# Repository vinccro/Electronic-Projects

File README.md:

# Electronic-Projects
Schematics and PCB board designs

The esp32SimpleRelay is a project that works from a 12v source probably a 
battery/solar setup. This is wifi so must be close to a wifi router or similar. 
Basicly a simple on/off relay, maybe for 12v led lights .
--currently esp32
--could use
  --zigbee (too expensive, long range, mesh network)
  --NRF24L01 (cheap, short range, star network)
  --433MHz modules (super cheap, long range, not a transceiver)
  --lora module ( expensive, long range, mesh network)
 
The tabelmini is a motor, valve etc. controller. Not designed yet to be for
industrial work. How it works: uses buttons to selected preprogrammed motor etc.
and user can select tests to be performed. or control the motor etc. directly. 
Possible connects to a PLC that controls the motor etc. and sends it commands 
wirelessly. or Directly connect using a port.
(working progress)

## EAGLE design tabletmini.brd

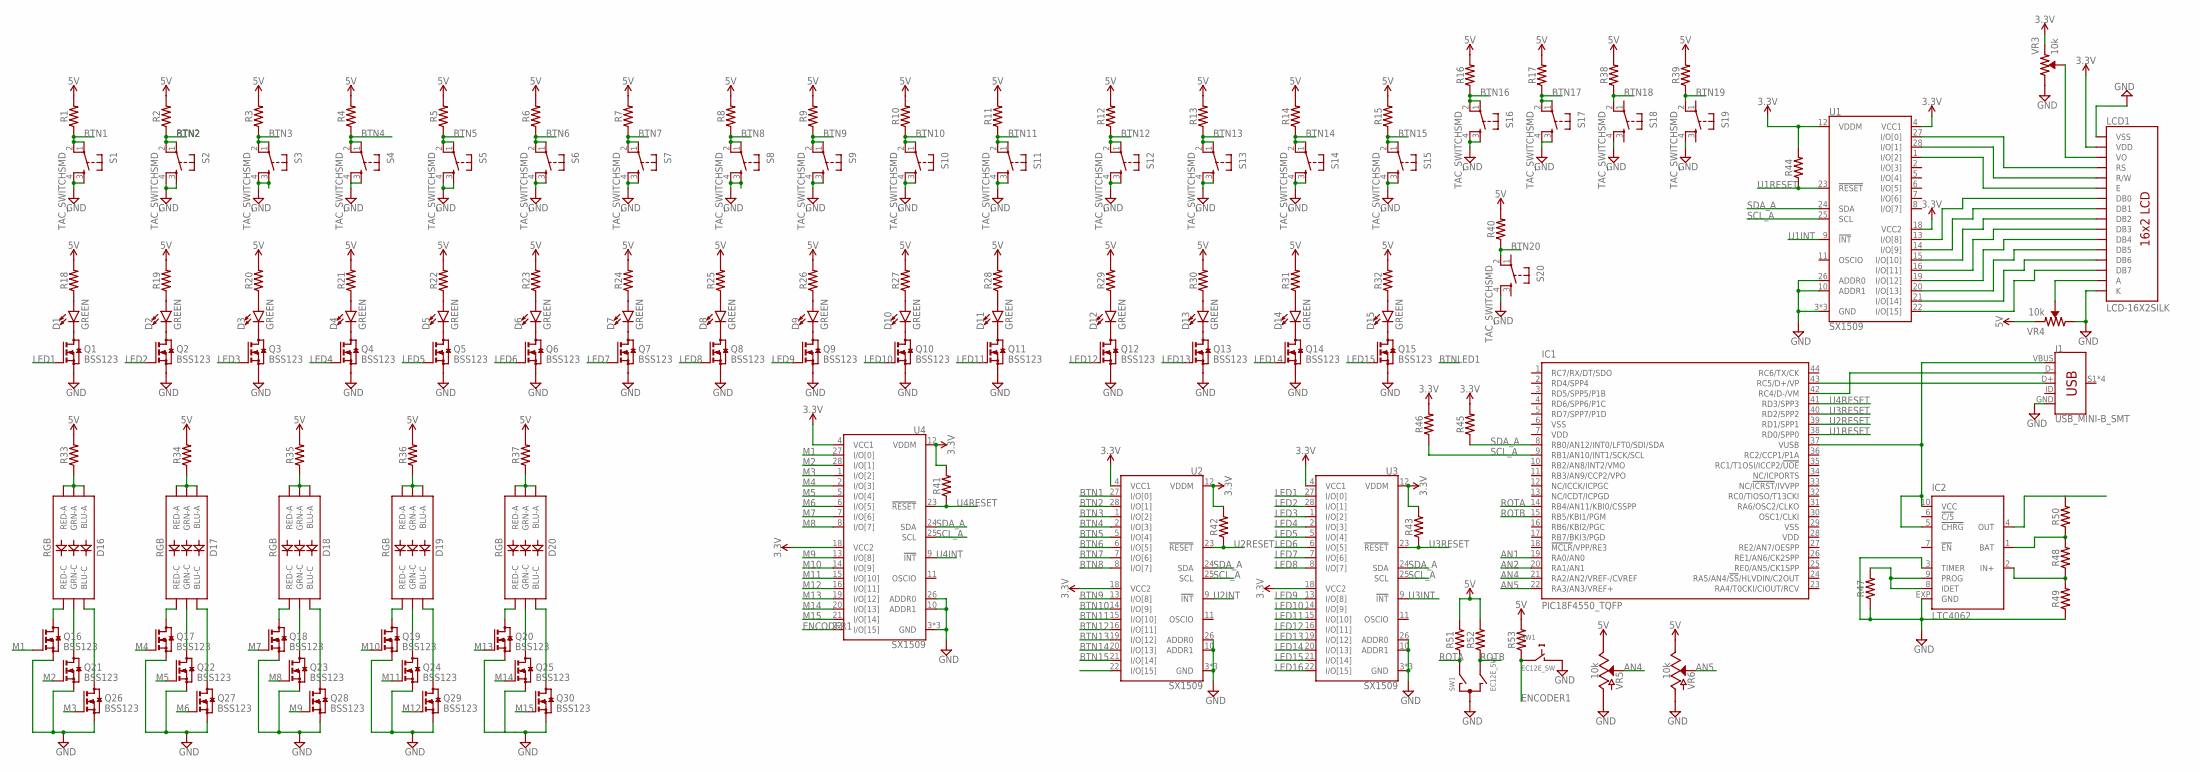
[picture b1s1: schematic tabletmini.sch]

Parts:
D1, D2, D3, D4, D5, D6, D7, D8, D9, D10, D11, D12, D13, D14, D15: GREEN; LED-1206
D16, D17, D18, D19, D20: RGB; PLCC-6-LED
IC1: PIC18F4550_TQFP; TQFP44
IC2: LTC4062; DFN10-3X3
J1: USB_MINI-B_SMT; USB-MINIB
LCD1: LCD-16X2SILK; LCD-16X2
Q1, Q2, Q3, Q4, Q5, Q6, Q7, Q8, Q9, Q10, Q11, Q12, Q13, Q14, Q15, Q16, Q17, Q18, Q19, Q20, Q21, Q22, Q23, Q24, Q25, Q26, Q27, Q28, Q29, Q30: BSS123; SOT23
R1, R2, R3, R4, R5, R6, R7, R8, R9, R10, R11, R12, R13, R14, R15, R16, R17, R18, R19, R20, R21, R22, R23, R24, R25, R26, R27, R28, R29, R30, R31, R32, R33, R34, R35, R36, R37, R38, R39, R40, R41, R42, R43, R44, R45, R46, R47, R48, R49, R50, R51, R52, R53: 1206
S1, S2, S3, S4, S5, S6, S7, S8, S9, S10, S11, S12, S13, S14, S15, S16, S17, S18, S19, S20: TAC_SWITCHSMD; TACTILE-SWITCH-SMD
SW1: EC12E_SW; ALPS_EC12E_SW
U1, U2, U3, U4: SX1509; QFN-28
VR3, VR4: 10k; TRIMPOT-SMD-3MM-CLOSED
VR5, VR6: 10k; POT-PTH-ALPS-KIT

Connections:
3.3V: LCD1.2 (VDD), R41.2, R42.2, R43.2, R44.2, R45.2, R46.2, U1.4 (VCC1), U1.12 (VDDM), U1.18 (VCC2), U2.4 (VCC1), U2.12 (VDDM), U2.18 (VCC2), U3.4 (VCC1), U3.12 (VDDM), U3.18 (VCC2), U4.4 (VCC1), U4.12 (VDDM), U4.18 (VCC2), VR3.1 (CCW)
5V: R1.2, R2.2, R3.2, R4.2, R5.2, R6.2, R7.2, R8.2, R9.2, R10.2, R11.2, R12.2, R13.2, R14.2, R15.2, R16.2, R17.2, R18.2, R19.2, R20.2, R21.2, R22.2, R23.2, R24.2, R25.2, R26.2, R27.2, R28.2, R29.2, R30.2, R31.2, R32.2, R33.2, R34.2, R35.2, R36.2, R37.2, R38.2, R39.2, R40.2, R51.2, R52.2, R53.2, VR4.1 (CCW), VR5.P$1 (E), VR6.P$1 (E)
AN1: IC1.19 (RA0/AN0)
AN2: IC1.20 (RA1/AN1)
AN4: IC1.21 (RA2/AN2/VREF-/CVREF), VR5.P$2 (S)
AN5: IC1.22 (RA3/AN3/VREF+), VR6.P$2 (S)
BTN1: R1.1, S1.1, S1.2, U2.27 (I/O[0])
BTN2: R2.1, S2.1, S2.2, U2.28 (I/O[1])
BTN3: R3.1, S3.1, S3.2, U2.1 (I/O[2])
BTN4: R4.1, S4.1, S4.2, U2.2 (I/O[3])
BTN5: R5.1, S5.1, S5.2, U2.5 (I/O[4])
BTN6: R6.1, S6.1, S6.2, U2.6 (I/O[5])
BTN7: R7.1, S7.1, S7.2, U2.7 (I/O[6])
BTN8: R8.1, S8.1, S8.2, U2.8 (I/O[7])
BTN9: R9.1, S9.1, S9.2, U2.13 (I/O[8])
BTN10: R10.1, S10.1, S10.2, U2.14 (I/O[9])
BTN11: R11.1, S11.1, S11.2, U2.15 (I/O[10])
BTN12: R12.1, S12.1, S12.2, U2.16 (I/O[11])
BTN13: R13.1, S13.1, S13.2, U2.19 (I/O[12])
BTN14: R14.1, S14.1, S14.2, U2.20 (I/O[13])
BTN15: R15.1, S15.1, S15.2, U2.21 (I/O[14])
BTN16: R16.1, S16.1, S16.2
BTN17: R17.1, S17.1, S17.2
BTN18: R38.1, S18.2
BTN19: R39.1, S19.2
BTN20: R40.1, S20.2
ENCODER1: R53.1, SW1.E (2), U4.22 (I/O[15])
GND: IC2.3 (TIMER), IC2.EXP (GND), J1.GND, LCD1.1 (VSS), LCD1.16 (K), Q1.2 (S), Q2.2 (S), Q3.2 (S), Q4.2 (S), Q5.2 (S), Q6.2 (S), Q7.2 (S), Q8.2 (S), Q9.2 (S), Q10.2 (S), Q11.2 (S), Q12.2 (S), Q13.2 (S), Q14.2 (S), Q15.2 (S), Q16.2 (S), Q17.2 (S), Q18.2 (S), Q19.2 (S), Q20.2 (S), Q21.2 (S), Q22.2 (S), Q23.2 (S), Q24.2 (S), Q25.2 (S), Q26.2 (S), Q27.2 (S), Q28.2 (S), Q29.2 (S), Q30.2 (S), R47.1, R49.1, S1.3, S1.4, S2.3, S2.4, S3.3, S3.4, S4.3, S4.4, S5.3, S5.4, S6.3, S6.4, S7.3, S7.4, S8.3, S8.4, S9.3, S9.4, S10.3, S10.4, S11.3, S11.4, S12.3, S12.4, S13.3, S13.4, S14.3, S14.4, S15.3, S15.4, S16.3, S16.4, S17.3, S17.4, S18.4, S19.4, S20.4, SW1.C, SW1.D (1), U1.3 (GND), U1.10 (ADDR1), U1.17 (GND), U1.26 (ADDR0), U1.29 (GND), U2.3 (GND), U2.10 (ADDR1), U2.17 (GND), U2.26 (ADDR0), U2.29 (GND), U3.3 (GND), U3.10 (ADDR1), U3.17 (GND), U3.26 (ADDR0), U3.29 (GND), U4.3 (GND), U4.10 (ADDR1), U4.17 (GND), U4.26 (ADDR0), U4.29 (GND), VR3.3 (CW), VR4.3 (CW), VR5.P$3 (A), VR6.P$3 (A)
LED1: Q1.1 (G), U3.27 (I/O[0])
LED2: Q2.1 (G), U3.28 (I/O[1])
LED3: Q3.1 (G), U3.1 (I/O[2])
LED4: Q4.1 (G), U3.2 (I/O[3])
LED5: Q5.1 (G), U3.5 (I/O[4])
LED6: Q6.1 (G), U3.6 (I/O[5])
LED7: Q7.1 (G), U3.7 (I/O[6])
LED8: Q8.1 (G), U3.8 (I/O[7])
LED9: Q9.1 (G), U3.13 (I/O[8])
LED10: Q10.1 (G), U3.14 (I/O[9])
LED11: Q11.1 (G), U3.15 (I/O[10])
LED12: Q12.1 (G), U3.16 (I/O[11])
LED13: Q13.1 (G), U3.19 (I/O[12])
LED14: Q14.1 (G), U3.20 (I/O[13])
LED15: Q15.1 (G), U3.21 (I/O[14])
LED16: U3.22 (I/O[15])
M1: Q16.1 (G), U4.27 (I/O[0])
M2: Q21.1 (G), U4.28 (I/O[1])
M3: Q26.1 (G), U4.1 (I/O[2])
M4: Q17.1 (G), U4.2 (I/O[3])
M5: Q22.1 (G), U4.5 (I/O[4])
M6: Q27.1 (G), U4.6 (I/O[5])
M7: Q18.1 (G), U4.7 (I/O[6])
M8: Q23.1 (G), U4.8 (I/O[7])
M9: Q28.1 (G), U4.13 (I/O[8])
M10: Q19.1 (G), U4.14 (I/O[9])
M11: Q24.1 (G), U4.15 (I/O[10])
M12: Q29.1 (G), U4.16 (I/O[11])
M13: Q20.1 (G), U4.19 (I/O[12])
M14: Q25.1 (G), U4.20 (I/O[13])
M15: Q30.1 (G), U4.21 (I/O[14])
unnamed: IC1.37 (VUSB), IC2.5 (!CHRG), IC2.10 (VCC), J1.VBUS
unnamed: IC1.42 (RC4/D-/VM), J1.D-
unnamed: IC1.43 (RC5/D+/VP), J1.D+
unnamed: LCD1.4 (RS), U1.27 (I/O[0])
unnamed: LCD1.5 (R/W), U1.28 (I/O[1])
unnamed: LCD1.6 (E), U1.1 (I/O[2])
unnamed: LCD1.7 (DB0), U1.13 (I/O[8])
unnamed: LCD1.8 (DB1), U1.14 (I/O[9])
unnamed: LCD1.9 (DB2), U1.15 (I/O[10])
unnamed: LCD1.10 (DB3), U1.16 (I/O[11])
unnamed: LCD1.11 (DB4), U1.19 (I/O[12])
unnamed: LCD1.12 (DB5), U1.20 (I/O[13])
unnamed: LCD1.13 (DB6), U1.21 (I/O[14])
unnamed: LCD1.14 (DB7), U1.22 (I/O[15])
unnamed: IC2.2 (IN+), R48.1, R49.2
unnamed: LCD1.15 (A), VR4.2 (WIPER)
unnamed: LCD1.3 (VO), VR3.2 (WIPER)
unnamed: IC2.1 (BAT), R48.2, R50.1
unnamed: IC2.8 (IDET), IC2.9 (PROG), R47.2
unnamed: D1.C, Q1.3 (D)
unnamed: D1.A, R18.1
unnamed: D2.C, Q2.3 (D)
unnamed: D2.A, R19.1
unnamed: D3.C, Q3.3 (D)
unnamed: D3.A, R20.1
unnamed: D4.C, Q4.3 (D)
unnamed: D4.A, R21.1
unnamed: D5.C, Q5.3 (D)
unnamed: D5.A, R22.1
unnamed: D6.C, Q6.3 (D)
unnamed: D6.A, R23.1
unnamed: D7.C, Q7.3 (D)
unnamed: D7.A, R24.1
unnamed: D8.C, Q8.3 (D)
unnamed: D8.A, R25.1
unnamed: D9.C, Q9.3 (D)
unnamed: D9.A, R26.1
unnamed: D10.C, Q10.3 (D)
unnamed: D10.A, R27.1
unnamed: D11.C, Q11.3 (D)
unnamed: D11.A, R28.1
unnamed: D12.C, Q12.3 (D)
unnamed: D12.A, R29.1
unnamed: D13.C, Q13.3 (D)
unnamed: D13.A, R30.1
unnamed: D14.C, Q14.3 (D)
unnamed: D14.A, R31.1
unnamed: D15.C, Q15.3 (D)
unnamed: D15.A, R32.1
unnamed: D16.AB (BLU-A), D16.AR (RED-A), R33.1
unnamed: D17.AB (BLU-A), D17.AR (RED-A), R34.1
unnamed: D18.AB (BLU-A), D18.AR (RED-A), R35.1
unnamed: D19.AB (BLU-A), D19.AR (RED-A), R36.1
unnamed: D20.AB (BLU-A), D20.AR (RED-A), R37.1
unnamed: D16.CR (RED-C), Q16.3 (D)
unnamed: D16.CG (GRN-C), Q21.3 (D)
unnamed: D16.CB (BLU-C), Q26.3 (D)
unnamed: D17.CR (RED-C), Q17.3 (D)
unnamed: D17.CG (GRN-C), Q22.3 (D)
unnamed: D17.CB (BLU-C), Q27.3 (D)
unnamed: D18.CR (RED-C), Q18.3 (D)
unnamed: D18.CG (GRN-C), Q23.3 (D)
unnamed: D18.CB (BLU-C), Q28.3 (D)
unnamed: D19.CR (RED-C), Q19.3 (D)
unnamed: D19.CG (GRN-C), Q24.3 (D)
unnamed: D19.CB (BLU-C), Q29.3 (D)
unnamed: D20.CR (RED-C), Q20.3 (D)
unnamed: D20.CG (GRN-C), Q25.3 (D)
unnamed: D20.CB (BLU-C), Q30.3 (D)
ROTA: IC1.14 (RB4/AN11/KBI0/CSSPP), R51.1, SW1.A
ROTB: IC1.15 (RB5/KBI1/PGM), R52.1, SW1.B
SCL_A: IC1.9 (RB1/AN10/INT1/SCK/SCL), R46.1, U1.25 (SCL), U2.25 (SCL), U3.25 (SCL), U4.25 (SCL)
SDA_A: IC1.8 (RB0/AN12/INT0/LFT0/SDI/SDA), R45.1, U1.24 (SDA), U2.24 (SDA), U3.24 (SDA), U4.24 (SDA)
U1INT: U1.9 (!INT)
U1RESET: IC1.38 (RD0/SPP0), R44.1, U1.23 (!RESET)
U2INT: U2.9 (!INT)
U2RESET: IC1.39 (RD1/SPP1), R42.1, U2.23 (!RESET)
U3INT: U3.9 (!INT)
U3RESET: IC1.40 (RD2/SPP2), R43.1, U3.23 (!RESET)
U4INT: U4.9 (!INT)
U4RESET: IC1.41 (RD3/SPP3), R41.1, U4.23 (!RESET)
VDD: IC1.7 (VDD), IC1.28 (VDD)
VSS: IC1.6 (VSS), IC1.29 (VSS)

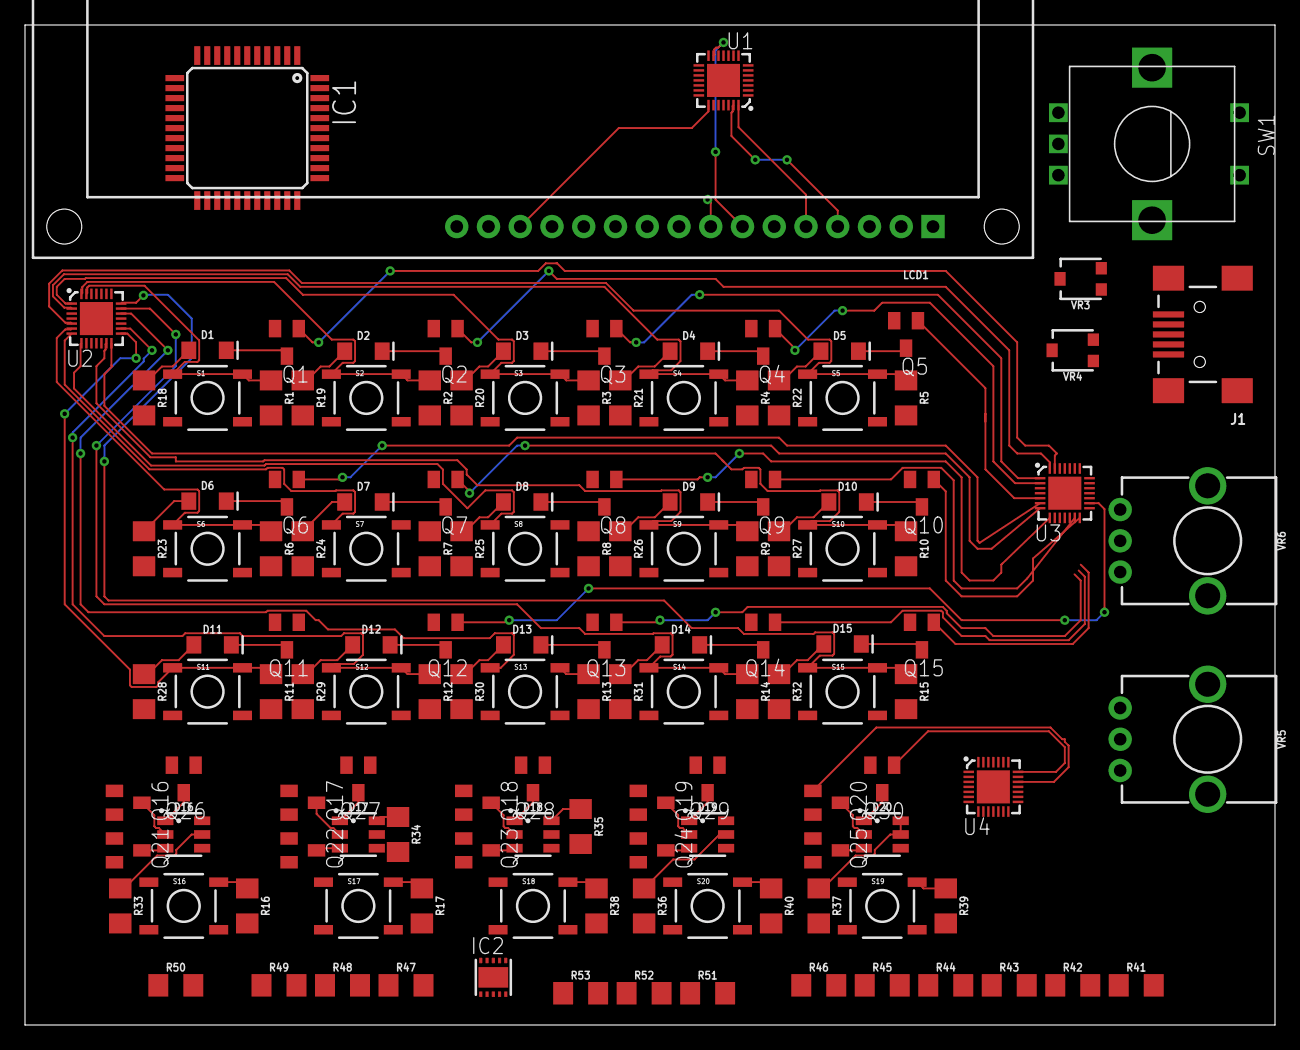
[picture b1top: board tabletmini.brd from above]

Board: 2 copper layers, 100.0 x 80.0 mm, 136 parts (0 on the bottom side), 135 nets.

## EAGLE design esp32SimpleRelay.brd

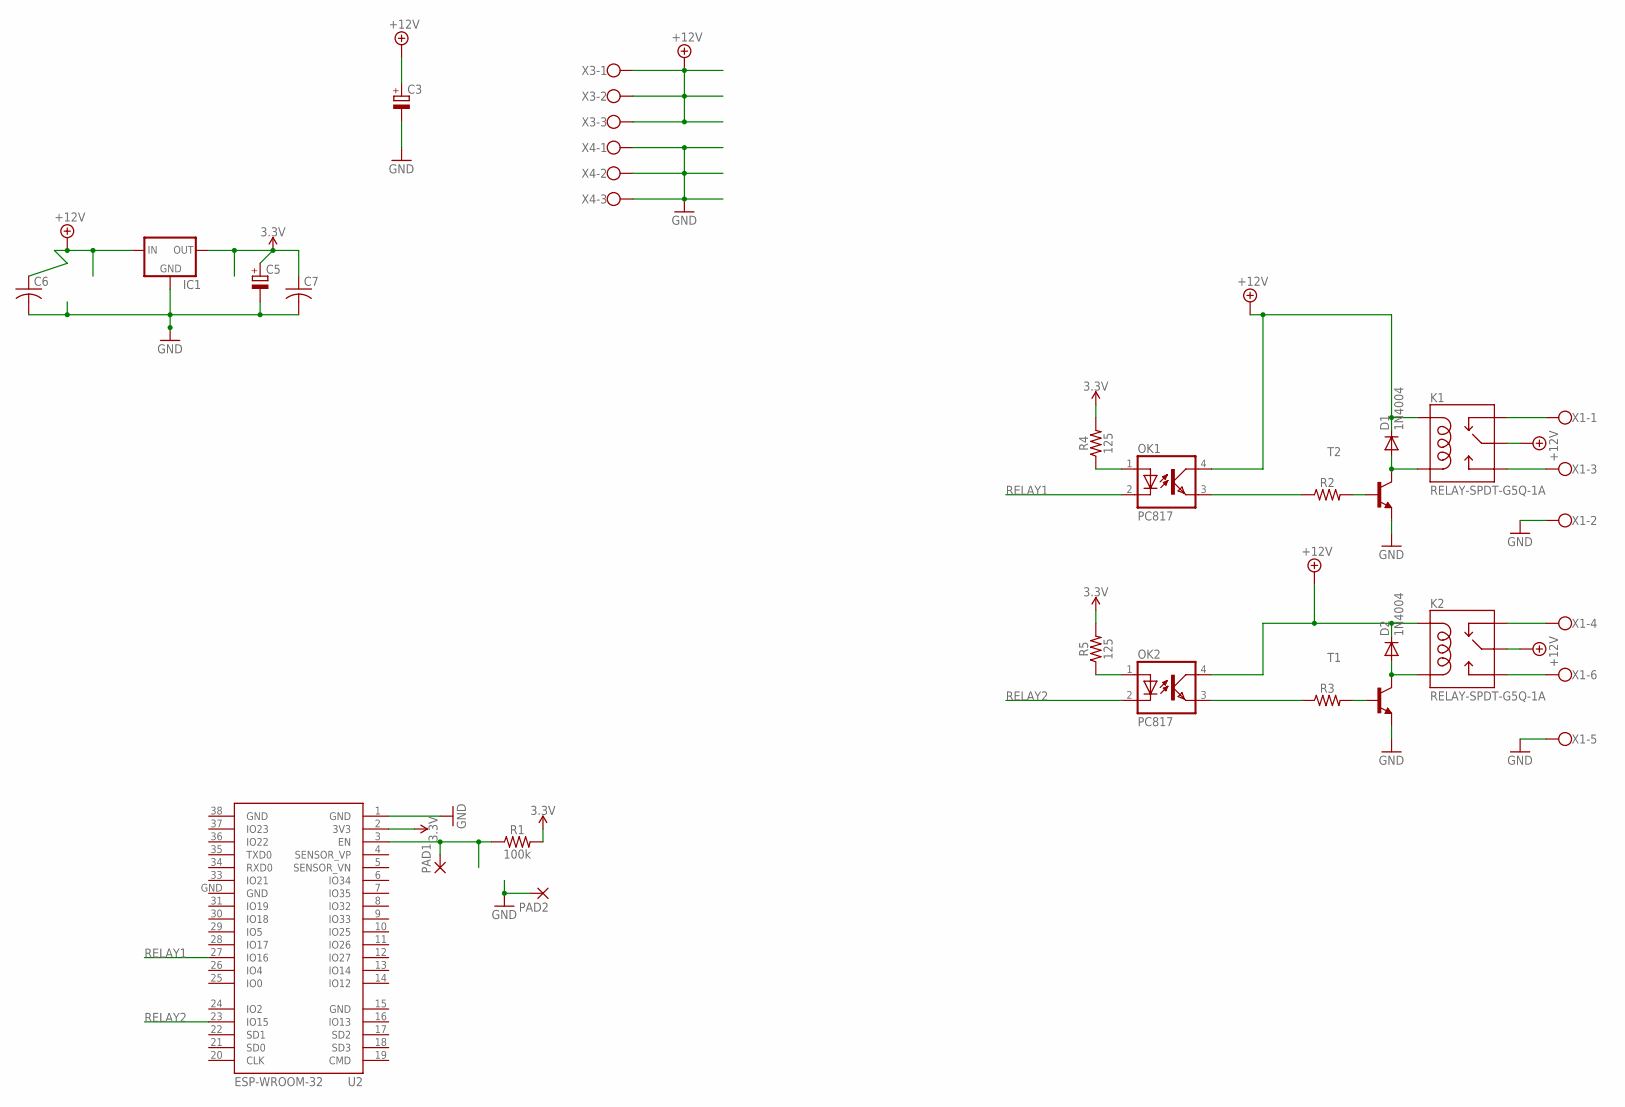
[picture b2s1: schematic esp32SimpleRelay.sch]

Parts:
C3: CPOL-EUE3.5-8; E3,5-8
C5: CPOL-EUE5-6; E5-6
C6, C7: C-US050-025X075; C050-025X075
D1, D2: 1N4004; DO41-10
IC1: 78LXX
K1, K2: RELAY-SPDT-G5Q-1A; RELAY-G5Q
OK1, OK2: PC817; DIL04
PAD1, PAD2: 1,6/0,9
R1: 100k; 0603
R2, R3: AXIAL-0.3
R4, R5: 125; AXIAL-0.3
T1, T2: -NPN-TO92; TO92
U2: ESP-WROOM-32
X1: W237-6
X3, X4: W237-103

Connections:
3.3V: C5.+, C7.1, IC1.OUT, R1.2, R4.P$2 (2), R5.P$2 (2), U2.2 (3V3)
+12V: C3.+, C6.1, D1.C, D2.C, IC1.IN, K1.2 (MAIN), K1.5 (COIL1), K2.2 (MAIN), K2.5 (COIL1), OK1.4 (COL), OK2.4 (COL), X3.1, X3.2, X3.3
GND: C3.-, C5.-, C6.2, C7.2, IC1.GND, PAD2.1, T1.1 (E), T2.1 (E), U2.1 (GND), U2.15 (GND), U2.38 (GND), U2.GND, X1.2, X1.5, X4.1, X4.2, X4.3
unnamed: K1.4 (NC), X1.1
unnamed: K1.3 (NO), X1.3
unnamed: PAD1.1, R1.1, U2.3 (EN)
unnamed: D1.A, K1.1 (COIL2), T2.3 (C)
unnamed: K2.4 (NC), X1.4
unnamed: D2.A, K2.1 (COIL2), T1.3 (C)
unnamed: OK1.1 (A), R4.P$1 (1)
unnamed: K2.3 (NO), X1.6
unnamed: R2.P$2 (2), T2.2 (B)
unnamed: OK2.3 (EMIT), R3.P$1 (1)
unnamed: R3.P$2 (2), T1.2 (B)
unnamed: OK1.3 (EMIT), R2.P$1 (1)
unnamed: OK2.1 (A), R5.P$1 (1)
RELAY1: OK1.2 (C), U2.27 (IO16)
RELAY2: OK2.2 (C), U2.23 (IO15)

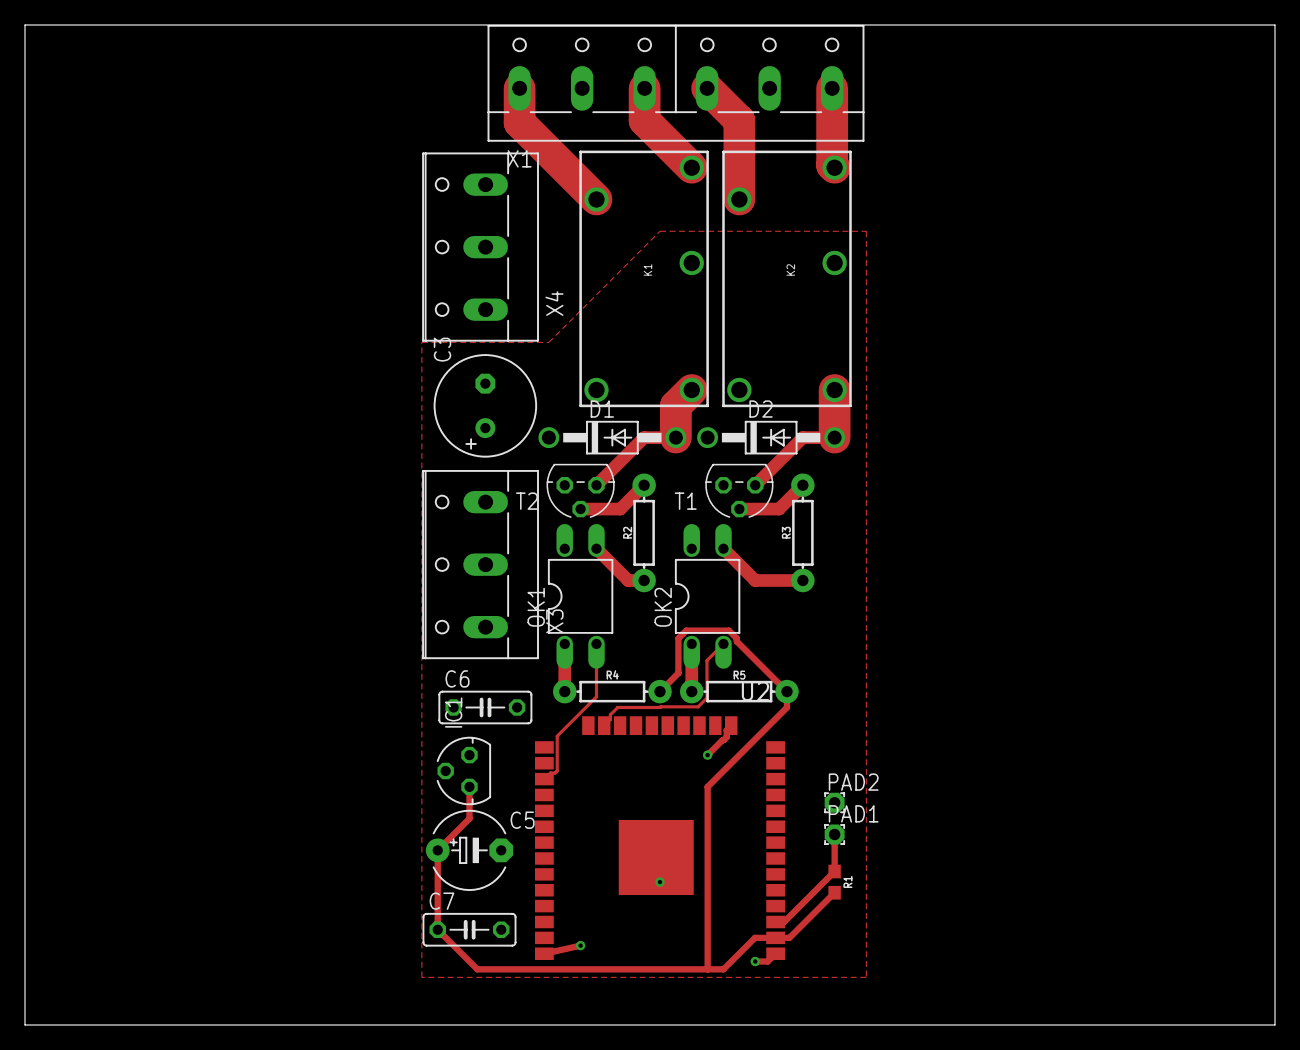
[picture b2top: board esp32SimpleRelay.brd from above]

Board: 2 copper layers, 100.0 x 80.0 mm, 24 parts (0 on the bottom side), 18 nets.

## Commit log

2018-04-07 first add
2018-04-09 new Project

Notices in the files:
parts and their libraries:
SparkFun-Retired: Licensing: Creative Commons ShareAlike 4.0 International - https://creativecommons.org/licenses/by-sa/4.0
esp32: Creative Commons Attribution-ShareAlike 4.0 International
